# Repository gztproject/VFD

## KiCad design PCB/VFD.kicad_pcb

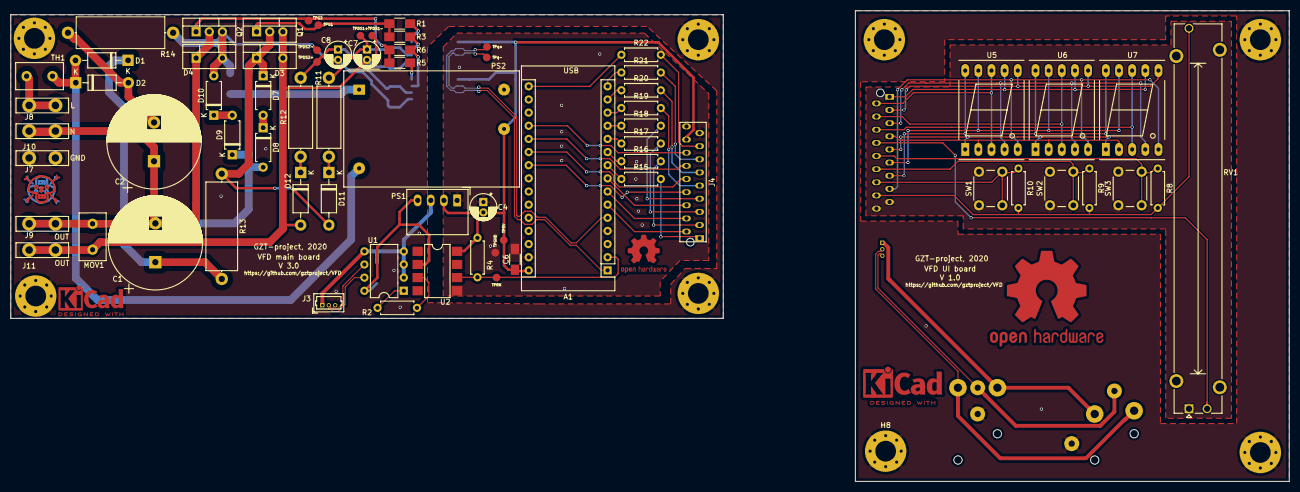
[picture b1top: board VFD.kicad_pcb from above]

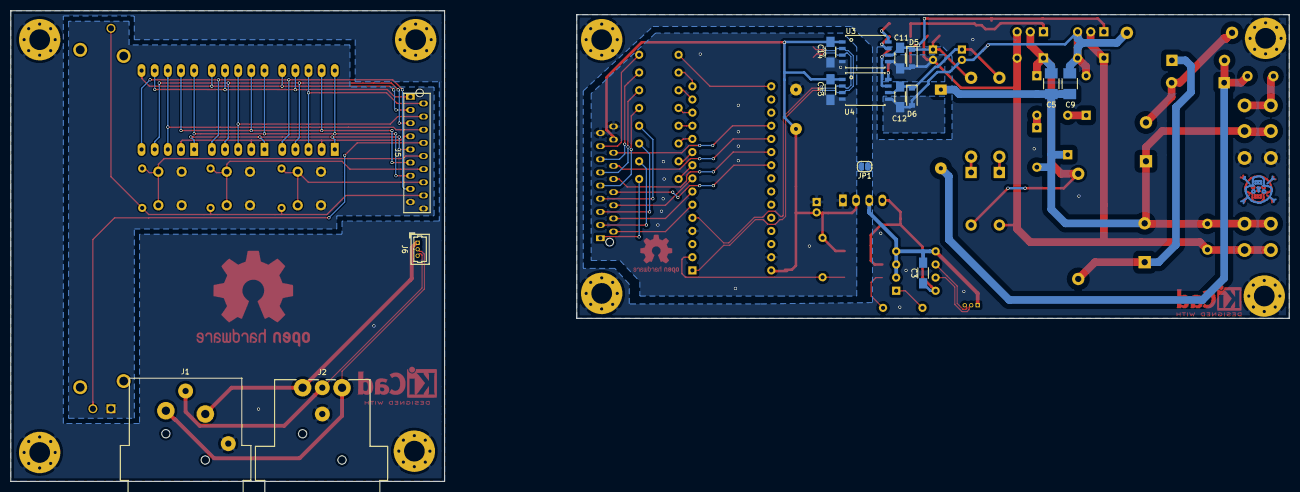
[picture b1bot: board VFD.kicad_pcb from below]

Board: 2 copper layers, 247.0 x 90.9 mm, 95 parts (16 on the bottom side), 72 nets.

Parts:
A1: Arduino_Nano_v3.x; Arduino_Nano
C1, C2: CP; CP_Radial_D18.0mm_P7.50mm
C3, C6: 100n; C_1206_HandSoldering
C4, C7, C8: 10u; CP_Radial_D5.0mm_P2.00mm
C5, C9: 100n, 500V; C_1210_HandSoldering
C11, C12: 1u, 25V; C_1206_HandSoldering
C13, C14: 100n, 25V; C_1206_HandSoldering
D1, D2, D11, D12: 1N4007; D_DO-41_SOD81_P10.16mm_Horizontal
D3, D4: D_Schottky; TO-220-2_Vertical
D5, D6: 15V; D_SOD-123
D7, D8, D9, D10: 200V; D_A-405_P7.62mm_Horizontal
H1, H2, H3, H4, H5, H6, H7, H8: MountingHole_Pad; MountingHole_4mm_Pad_Via
J1: XLR3_Ground; Jack_XLR_Neutrik_NC3FAAH2_Horizontal
J2: XLR3_Ground; Jack_XLR_Neutrik_NC3MAAH_Horizontal
J3, J6: Conn_01x03_Male; Molex_PicoBlade_53047-0310_03x1.25mm_Straight
J4, J5: Conn_02x09_Odd_Even; CONN-TE-MICROMATCH-9X2-PTH-BOSS
J7, J8, J9, J10, J11: Conn_01x01; FASTON_250_straight_male
JP1: SolderJumper_2_Open; SolderJumper-2_P1.3mm_Open_RoundedPad1.0x1.5mm
MOV1: 650V; C_Disc_D9.0mm_W5.0mm_P5.00mm
PS1: RFM0505S; DCDC-Conv_RECOM_R-78S-0.1
PS2: IRM-02-5; Converter_ACDC_MeanWell_IRM-02-xx_THT
Q1, Q2: IXA12IF1200PB; TO-220-3_Vertical
R1, R5: 3R3; R_1206_HandSoldering
R2: 1K; R_Axial_DIN0207_L6.3mm_D2.5mm_P7.62mm_Horizontal
R3, R6: 10R; R_1206_HandSoldering
R4: 4K7; R_Axial_DIN0207_L6.3mm_D2.5mm_P7.62mm_Horizontal
R8, R9, R10: 15k; R_Axial_DIN0207_L6.3mm_D2.5mm_P7.62mm_Horizontal
R11, R12: 110k; R_Axial_DIN0414_L11.9mm_D4.5mm_P15.24mm_Horizontal
R13, R14: 20; R_Axial_DIN0617_L17.0mm_D6.0mm_P20.32mm_Horizontal
R15, R16, R17, R18, R19, R20, R21, R22: 270; R_Axial_DIN0207_L6.3mm_D2.5mm_P7.62mm_Horizontal
RV1: 10k; Potentiometer_Bourns_PTA6043_Single_Slide
SW1, SW2, SW3: SW_Push; SW_PUSH_6mm_h7.3mm
TH1: 20; C_Disc_D9.0mm_W5.0mm_P5.00mm
TP5V: Conn_01x01; Measurement_Point_Round-SMD-Pad_Small
TPDS1+, TPDS1-, TPDS2+, TPDS2-: Conn_01x01; Measurement_Point_Round-SMD-Pad_Small
TPG1, TPG2: Conn_01x01; Measurement_Point_Round-SMD-Pad_Small
TPGND: Conn_01x01; Measurement_Point_Round-SMD-Pad_Small
TPRX: Conn_01x01; Measurement_Point_Round-SMD-Pad_Small
TPq+: Conn_01x01; Measurement_Point_Round-SMD-Pad_Small
TPq-: Conn_01x01; Measurement_Point_Round-SMD-Pad_Small
U1: SN75176BDR; DIP-8_W7.62mm
U2: 6N137; SMDIP-8_W7.62mm
U3, U4: 1EDIxxI12AH; Infineon_PG-DSO-8-59
U5, U6, U7: HDSP-5501; 7SegmentLED_LTS6760_LTS6780

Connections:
+5V: A1.30, C4.2, C6.1, C13.1, C14.1, J4.16, J5.16, PS1.2, PS2.4, R4.2, R8.2, R9.2, R10.2, RV1.3, TP5V.1, U2.8, U3.1, U4.1
+5VA: C3.1, PS1.4, U1.8, U2.2
/+400V: C1.1, D1.1, R13.2
/+DriverSupply: C7.1, C11.1, D5.1, R11.2, TPDS1+.1, U3.6
/+Gate: Q1.1, R1.2, R3.2, TPG1.1
/+IGBT: C5.1, D3.1, D7.1, D11.2, Q1.2, R13.1
/-400V: C2.2, D2.2, R14.2
/-DriverSupply: C8.1, C12.1, D6.1, R12.2, TPDS2+.1, U4.6
/-Gate: Q2.1, R5.2, R6.2, TPG2.1
/-IGBT: C8.2, C9.2, C12.2, D4.2, D6.2, D10.2, Q2.3, R14.1, TPDS2-.1, U4.5
/BTN1: A1.19, J4.14
/BTN2: A1.20, J4.12
/BTN3: A1.21, J4.10
/DMX+: J3.3, U1.6
/DMX-: J3.2, U1.7
/Disp-A: J4.1, R15.2
/Disp-B: J4.3, R16.2
/Disp-C: J4.5, R17.2
/Disp-CA1: A1.6, J4.2
/Disp-CA2: A1.7, J4.4
/Disp-CA3: A1.8, J4.6
/Disp-D: J4.7, R18.2
/Disp-DP: J4.15, R22.2
/Disp-E: J4.9, R19.2
/Disp-F: J4.11, R20.2
/Disp-G: J4.13, R21.2
/L_NTC: D1.2, D2.1, PS2.2, TH1.1
/MotL: C7.2, C11.2, D3.2, D4.1, D5.2, D12.2, J11.1, MOV1.1, Q1.3, Q2.2, TPDS1-.1, U3.5
/Pot: A1.22, J4.8
/Trig+: A1.1, TPq+.1, U3.2, U4.3
/Trig-: A1.5, TPq-.1, U3.3, U4.2
/UI/BTN1: J5.14, R10.1, SW1.2
/UI/BTN2: J5.12, R9.1, SW2.2
/UI/BTN3: J5.10, R8.1, SW3.2
/UI/DMX+: J1.2, J2.2, J6.2
/UI/DMX-: J1.3, J2.3, J6.3
/UI/Disp-A: J5.1, U5.7, U6.7, U7.7
/UI/Disp-B: J5.3, U5.6, U6.6, U7.6
/UI/Disp-C: J5.5, U5.4, U6.4, U7.4
/UI/Disp-CA1: J5.2, U5.3, U5.8
/UI/Disp-CA2: J5.4, U6.3, U6.8
/UI/Disp-CA3: J5.6, U7.3, U7.8
/UI/Disp-D: J5.7, U5.2, U6.2, U7.2
/UI/Disp-DP: J5.15, U5.5, U6.5, U7.5
/UI/Disp-E: J5.9, U5.1, U6.1, U7.1
/UI/Disp-F: J5.11, U5.9, U6.9, U7.9
/UI/Disp-G: J5.13, U5.10, U6.10, U7.10
/UI/Pot: J5.8, RV1.2
GND: A1.4, A1.29, C4.1, C6.2, C13.2, C14.2, J4.17, J4.18, J5.17, J5.18, JP1.2, PS1.1, PS2.3, RV1.1, SW1.1, SW2.1, SW3.1, TPGND.1, U2.5, U3.4, U4.4
GNDA: C3.2, J1.1, J2.1, J3.1, J6.1, PS1.3, U1.2, U1.3, U1.4, U1.5
GNDPWR: H1.1, H2.1, H3.1, H4.1, H5.1, H6.1, H7.1, H8.1, J1.G, J2.G, J7.1, JP1.1
LINE: J8.1, TH1.2
NEUT: C1.2, C2.1, C5.2, C9.1, D8.2, D9.1, J9.1, J10.1, MOV1.2, PS2.1
unnamed: A1.2, R4.1, TPRX.1, U2.6
unnamed: A1.9, R15.1
unnamed: A1.10, R16.1
unnamed: A1.11, R17.1
unnamed: A1.12, R18.1
unnamed: A1.13, R19.1
unnamed: A1.14, R20.1
unnamed: A1.15, R21.1
unnamed: A1.16, R22.1
unnamed: D7.2, D8.1
unnamed: D9.2, D10.1
unnamed: D11.1, R11.1
unnamed: D12.1, R12.1
unnamed: R1.1, U3.8
unnamed: R2.1, U2.3
unnamed: R2.2, U1.1
unnamed: R3.1, U3.7
unnamed: R5.1, U4.8
unnamed: R6.1, U4.7

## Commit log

2020-01-16 Some tests...
2020-01-16 More testing...
2020-01-16 Found the way to go :)
2020-01-16 Trying to find out the right function for PWM
2020-01-16 Lowered max duty cycle
2020-01-17 PWM drive done!
2020-01-17 Added some comments
2020-01-17 Better input range for width...
2020-01-17 Added PCB
2020-01-18 Added DMX library and some EEPROM stuff
2020-01-18 More work on UI
2020-01-18 Removed a debugging line
2020-02-03 Started work with actual PCB
2020-02-03 Updated PCB, added KiCad files
2020-02-03 PCB updates
2020-02-03 Started to work on DMX
2020-02-06 PCB V2.0
2020-02-06 Updated project
2020-02-13 Added some more inductive surge protection
2020-02-25 Changed the schema, new IGBTs and drivers
2020-02-26 Started reworking the PCB layout
2020-02-27 More work on PCB
2020-02-27 Added some testPoints
2020-02-28 More PCB fixes
2020-02-28 Fixed default value
2020-02-28 Ignoring autosaves
2020-04-21 Updated startup pin state, relative include path
2020-04-21 Updated some component values
2020-04-21 Added build test
